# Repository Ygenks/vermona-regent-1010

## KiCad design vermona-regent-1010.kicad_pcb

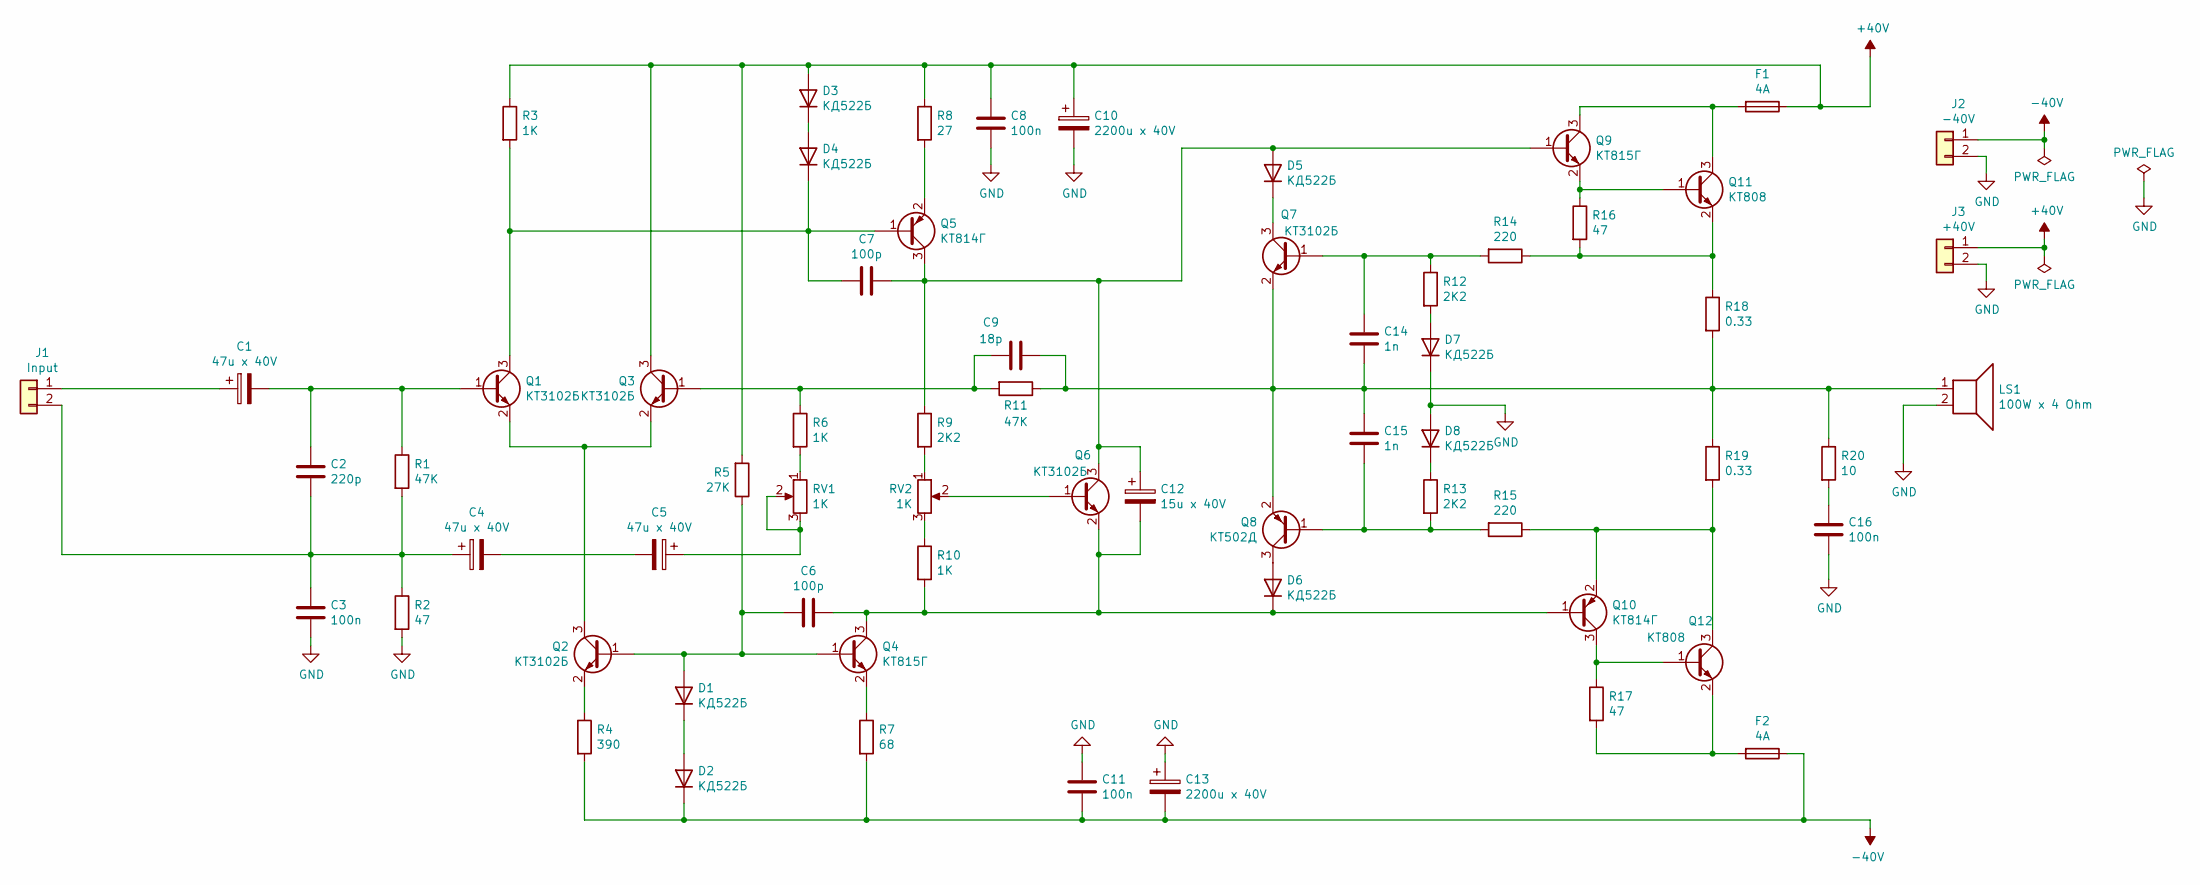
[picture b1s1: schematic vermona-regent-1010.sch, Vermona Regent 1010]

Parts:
C1, C4, C5: 47u x 40V; CP_Radial_D6.3mm_P2.50mm
C2: 220p; C_Rect_L7.0mm_W4.5mm_P5.00mm
C3, C8, C11, C16: 100n; C_Rect_L7.0mm_W4.5mm_P5.00mm
C6, C7: 100p; C_Rect_L7.0mm_W4.5mm_P5.00mm
C9: 18p; C_Rect_L4.6mm_W3.8mm_P2.50mm_MKS02_FKP02
C10, C13: 2200u x 40V; CP_Radial_D16.0mm_P7.50mm
C12: 15u x 40V; CP_Radial_D5.0mm_P2.00mm
C14, C15: 1n; C_Rect_L7.0mm_W4.5mm_P5.00mm
D1, D2, D3, D4, D5, D6, D7, D8: КД522Б; D_DO-15_P15.24mm_Horizontal
F1, F2: 4A; Fuseholder_Cylinder-5x20mm_Stelvio-Kontek_PTF78_Horizontal_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
J1: Input; PinHeader_1x02_P2.54mm_Vertical
J2: -40V; PinHeader_1x02_P2.54mm_Vertical
J3: +40V; PinHeader_1x02_P2.54mm_Vertical
LS1: 100W x 4 Ohm; PinHeader_1x02_P2.54mm_Vertical
Q1, Q2, Q3, Q6, Q7: КТ3102Б; TO-92
Q4, Q9: КТ815Г; TO-126-3_Vertical
Q5, Q10: КТ814Г; TO-126-3_Vertical
Q8: КТ502Д; TO-92
Q11, Q12: КТ808; PinHeader_1x03_P2.54mm_Vertical
R1, R11: 47K; R_Axial_DIN0309_L9.0mm_D3.2mm_P12.70mm_Horizontal
R2, R16, R17: 47; R_Axial_DIN0309_L9.0mm_D3.2mm_P12.70mm_Horizontal
R3, R6, R10: 1K; R_Axial_DIN0309_L9.0mm_D3.2mm_P12.70mm_Horizontal
R4: 390; R_Axial_DIN0309_L9.0mm_D3.2mm_P12.70mm_Horizontal
R5: 27K; R_Axial_DIN0309_L9.0mm_D3.2mm_P12.70mm_Horizontal
R7: 68; R_Axial_DIN0309_L9.0mm_D3.2mm_P12.70mm_Horizontal
R8: 27; R_Axial_DIN0309_L9.0mm_D3.2mm_P12.70mm_Horizontal
R9, R12, R13: 2K2; R_Axial_DIN0309_L9.0mm_D3.2mm_P12.70mm_Horizontal
R14, R15: 220; R_Axial_DIN0309_L9.0mm_D3.2mm_P12.70mm_Horizontal
R18, R19: 0.33; R_Axial_DIN0414_L11.9mm_D4.5mm_P20.32mm_Horizontal
R20: 10; R_Axial_DIN0309_L9.0mm_D3.2mm_P12.70mm_Horizontal
RV1, RV2: 1K; Potentiometer_Piher_PT-10-V10_Vertical

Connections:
40V: C8.1, C10.1, D3.2 (A), F1.1, J3.1, Q3.3 (C), R3.1, R5.2, R8.1
-40V: C11.2, C13.2, D2.1 (K), F2.1, J2.1, R4.2, R7.2
GND: C3.2, C8.2, C10.2, C11.1, C13.1, C16.2, D7.1 (K), D8.2 (A), J2.2, J3.2, LS1.2, R2.2
unnamed: C1.1, J1.1
unnamed: C1.2, C2.1, Q1.1 (B), R1.1
unnamed: C2.2, C3.1, C4.1, J1.2, R1.2, R2.1
unnamed: C4.2, C5.2
unnamed: C5.1, RV1.2, RV1.3
unnamed: C6.2, D1.2 (A), Q2.1 (B), Q4.1 (B), R5.1
unnamed: C7.1, D4.1 (K), Q1.3 (C), Q5.1 (B), R3.2
unnamed: C9.2, Q3.1 (B), R6.1, R11.2
unnamed: C7.2, C12.1, D5.2 (A), Q5.3 (C), Q6.3 (C), Q9.1 (B), R9.1
unnamed: C6.1, C12.2, D6.1 (K), Q4.3 (C), Q6.2 (E), Q10.1 (B), R10.2
unnamed: C14.1, Q7.1 (B), R12.1, R14.2
unnamed: C9.1, C14.2, C15.1, LS1.1, Q7.2 (E), Q8.2 (E), R11.1, R18.2, R19.1, R20.1
unnamed: C15.2, Q8.1 (B), R13.2, R15.2
unnamed: C16.1, R20.2
unnamed: D1.1 (K), D2.2 (A)
unnamed: D3.1 (K), D4.2 (A)
unnamed: D5.1 (K), Q7.3 (C)
unnamed: D6.2 (A), Q8.3 (C)
unnamed: D7.2 (A), R12.2
unnamed: D8.1 (K), R13.1
unnamed: F1.2, Q9.3 (C), Q11.3 (C)
unnamed: F2.2, Q12.2 (E), R17.2
unnamed: Q1.2 (E), Q2.3 (C), Q3.2 (E)
unnamed: Q2.2 (E), R4.1
unnamed: Q4.2 (E), R7.1
unnamed: Q5.2 (E), R8.2
unnamed: Q6.1 (B), RV2.2
unnamed: Q10.2 (E), Q12.3 (C), R15.1, R19.2
unnamed: Q10.3 (C), Q12.1 (B), R17.1
unnamed: Q9.2 (E), Q11.1 (B), R16.1
unnamed: Q11.2 (E), R14.1, R16.2, R18.1
unnamed: R6.2, RV1.1
unnamed: R9.2, RV2.1
unnamed: R10.1, RV2.3

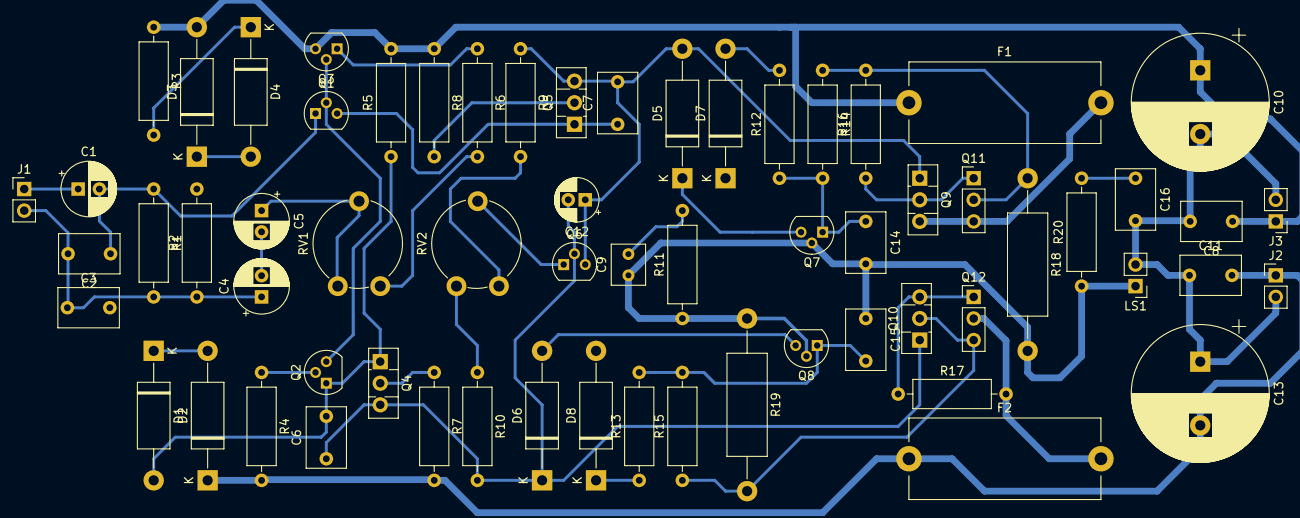
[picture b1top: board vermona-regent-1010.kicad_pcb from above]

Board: 2 copper layers, 64 parts (0 on the bottom side), 37 nets.

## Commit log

2021-06-08 Add schematic title
2021-06-15 Start drawing schematics
2021-06-18 Draw lower shoulder
2021-06-20 Finish schematics
2021-06-21 Trace differential amp
2021-06-22 Finish routing amp
